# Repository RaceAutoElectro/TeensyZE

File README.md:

# TeensyZE
Teensy Adapter with : CAN , SD , BLUETOOTH , OLED LCD , RTC , DB9-OBD2 .

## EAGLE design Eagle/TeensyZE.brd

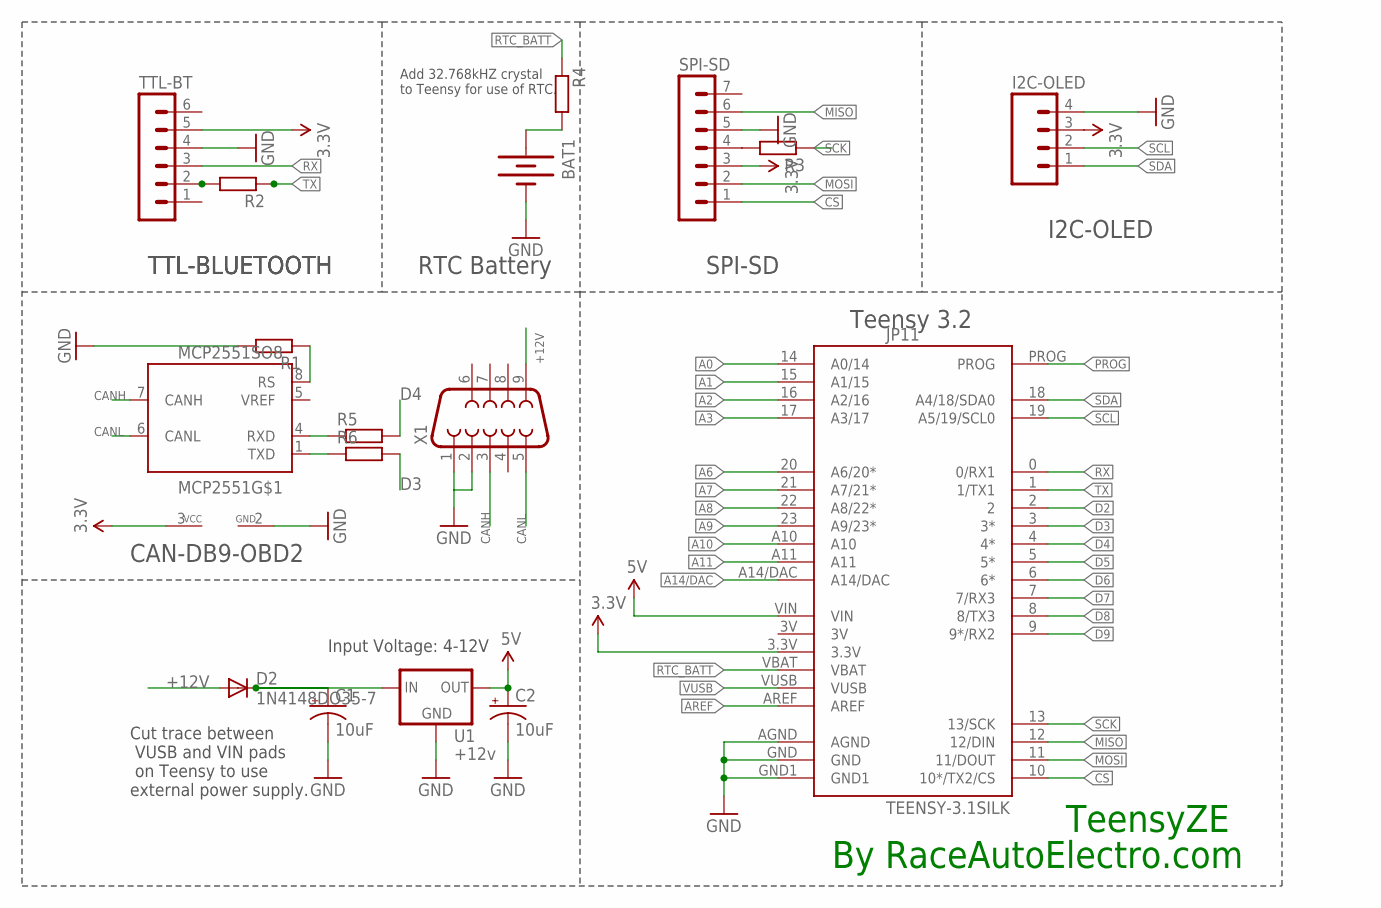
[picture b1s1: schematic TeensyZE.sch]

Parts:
BAT1: BATTERY12PTH; BATTCON_12MM_PTH
C1, C2: 10uF; CPOL-RADIAL-10UF-25V
D2: 1N4148DO35-7; DO35-7
I2C-OLED: M04PTH; 1X04
JP11: TEENSY-3.1SILK; TEENSY-3.1
MCP2551: MCP2551SO8; SO08
R1, R2, R3, R4, R5, R6: R-EU_R0805; R0805
SPI-SD: MA07-1
TTL-BT: MA06-1
U1: +12v; TO-252
X1: F09HP

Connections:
3.3V: I2C-OLED.3, JP11.3.3V, MCP2551.3 (VCC), SPI-SD.3, TTL-BT.5
5V: C2.1 (+), JP11.VIN, U1.2 (OUT)
+12V: D2.A, X1.9
A0: JP11.14 (A0/14)
A1: JP11.15 (A1/15)
A2: JP11.16 (A2/16)
A3: JP11.17 (A3/17)
A6: JP11.20 (A6/20*)
A7: JP11.21 (A7/21*)
A8: JP11.22 (A8/22*)
A9: JP11.23 (A9/23*)
A10: JP11.A10
A11: JP11.A11
A14/DAC: JP11.A14/DAC
AREF: JP11.AREF
CANH: MCP2551.7 (CANH), X1.3
CANL: MCP2551.6 (CANL), X1.5
CS: JP11.10 (10*/TX2/CS), SPI-SD.1
D2: JP11.2
D3: JP11.3 (3*), R6.2
D4: JP11.4 (4*), R5.2
D5: JP11.5 (5*)
D6: JP11.6 (6*)
D7: JP11.7 (7/RX3)
D8: JP11.8 (8/TX3)
D9: JP11.9 (9*/RX2)
GND: BAT1.GND (-), C1.2 (-), C2.2 (-), I2C-OLED.4, JP11.AGND, JP11.GND, JP11.GND1, MCP2551.2 (GND), R1.2, SPI-SD.5, TTL-BT.4, U1.3 (GND), X1.1, X1.2
MISO: JP11.12 (12/DIN), SPI-SD.6
MOSI: JP11.11 (11/DOUT), SPI-SD.2
unnamed: MCP2551.8 (RS), R1.1
unnamed: R2.2, TTL-BT.2
unnamed: R3.2, SPI-SD.4
unnamed: MCP2551.4 (RXD), R5.1
unnamed: MCP2551.1 (TXD), R6.1
unnamed: BAT1.VCC@1 (+), R4.2
PROG: JP11.PROG
RTC_BATT: JP11.VBAT, R4.1
RX: JP11.0 (0/RX1), TTL-BT.3
SCK: JP11.13 (13/SCK), R3.1
SCL: I2C-OLED.2, JP11.19 (A5/19/SCL0)
SDA: I2C-OLED.1, JP11.18 (A4/18/SDA0)
TX: JP11.1 (1/TX1), R2.1
VRAW: C1.1 (+), D2.C, U1.1 (IN)
VUSB: JP11.VUSB

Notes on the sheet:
Input Voltage: 4-12V
Add 32.768kHZ crystal to Teensy for use of RTC.
Cut trace between VUSB and VIN pads on Teensy to use external power supply.
Teensy 3.2
RTC Battery
I2C-OLED
TeensyZE
SPI-SD
TTL-BLUETOOTH
CAN-DB9-OBD2
By RaceAutoElectro.com

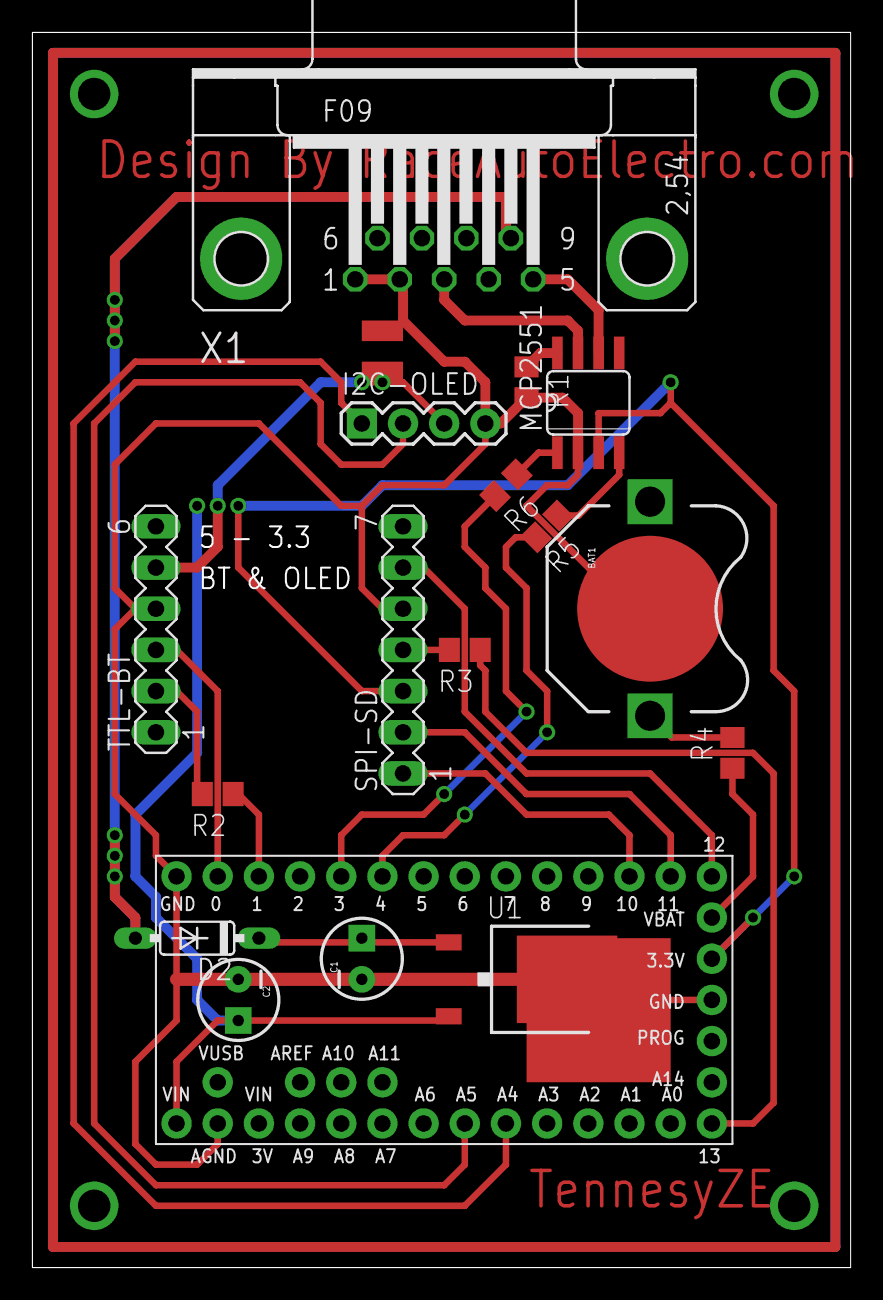
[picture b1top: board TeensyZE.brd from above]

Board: 2 copper layers, 50.5 x 76.2 mm, 17 parts (1 on the bottom side), 24 nets.

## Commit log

2016-01-14 Pictures

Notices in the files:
parts and their libraries:
SparkFun-Electromechanical: Licensing: Creative Commons ShareAlike 4.0 International - https://creativecommons.org/licenses/by-sa/4.0
